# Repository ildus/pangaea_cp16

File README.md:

# Cabinet simulator (on impulse responses) based on AMT Pangaea CP-16

Contains schematic and pcb. Based on debugging board of CP16.

## Basic components.

* Pangaea CP-16
* NE5532D (3pcs) operational amplifiers.
* 0 Ohm 2512 SMD resistors
* 1206 SMD resistors
* 0805 SMD capacitors
* Electrolytic capacitors
* 15pin (pangaea), 4pin (pangaea control), 6pin (double potenciometer), and 2pcs of 2pin headers.
* 3pcs of 6.3mm audio jacks.
* 1pic of USB connector.

For the values of resistors and capacitors check the schematic.

## Pangaea CP-16 (copied from AMT website).

AMT Pangaea CP-16 module lets you to emulate any Guitar Cabinet sounding by loading appropriate
Guitar Cabinets’ Impulse Responses (IRs).

You can load up to 16 different Guitar Cabinets’ IRs in the module’s memory and choose the desired
one in the right moment. You can load IRs in the CP-16 memory and control their parameters via USB.

## Important note

As you can see on the image above, the pin header soldered on the side opposite to side with capacitor, that's not optimal and takes twice as much height. The PCB is designed to use with CP16 where pin header is soldered on the side of capacitor so the whole pcb can be put to usual aluminum case.

## PCB

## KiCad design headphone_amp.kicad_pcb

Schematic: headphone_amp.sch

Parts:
C1, C6, C13, C22, C24, C29, C30: 100n; C_0805_2012Metric
C2, C3, C4, C5: 47u; CP_Radial_D4.0mm_P2.00mm
C9, C10: 4.7u; C_0805_2012Metric
C12, C25, C26: 22p; C_0805_2012Metric
C14, C15: 470p; C_0805_2012Metric
C16, C17, C19: 1.2n; C_0805_2012Metric
C18: 0.22u; C_0805_2012Metric
C20, C21: 100p; C_0805_2012Metric
C27, C28: 220u; CP_Radial_D6.3mm_P2.50mm
D1: red; PinSocket_1x02_P2.00mm_Vertical
D2: BAV99; SOT-23
J1: btn; PinSocket_1x02_P2.54mm_Vertical
J2: AUX_IN; Jack6P
J3: IN; Jack6P
J4: pangea_cp16; PinSocket_1x15_P2.54mm_Vertical
J5: USB_A
J6: OUT; Jack6P
J7: PWR; PinSocket_1x02_P2.54mm_Vertical
J10: Conn_01x04; PinSocket_1x04_P2.54mm_Vertical
R1, R23: 68K; R_1206_3216Metric
R2, R30, R31, R36, R38, R39, R40: 0; R_2512_6332Metric
R5, R8, R9, R10, R11, R12, R26, R27, R34, R35: 100k; R_1206_3216Metric
R7: 2m; R_1206_3216Metric
R13: 150k; R_1206_3216Metric
R14, R15, R16, R17, R19, R20, R21, R22: 10k; R_1206_3216Metric
R18: 100; R_1206_3216Metric
R24, R25: 390k; R_1206_3216Metric
R28, R29: 10; R_1206_3216Metric
R32, R33: 2k; R_1206_3216Metric
R37: 3k; R_1206_3216Metric
RV2: B50K; PinSocket_1x06_P2.54mm_Vertical
U1, U3, U4: NE5532; SO-8_5.3x6.2mm_P1.27mm

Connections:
+4V: R9.2, R11.1, R12.1, R21.1, R22.1, R39.1, R39.2, U1.1, U1.2 (-)
+9V: C1.1, C2.1, C13.1, C22.2, C24.1, D1.2, D2.2, J4.15, J7.2, R2.1, R2.2, R5.2, R30.1, R30.2, R31.1, R31.2, R36.1, R36.2, U1.8 (V+), U3.8 (V+), U4.8 (V+)
/ain: J4.4, R38.1
/aoutl: C9.2, J4.2
/aoutr: C10.2, J4.1
/aux_l: C25.2, R24.2, R26.1, R35.1, U4.2 (-)
/aux_r: C26.2, R25.2, R27.1, R34.1, U4.6 (-)
/outl: J6.1, R28.1
/outr: J6.2, R29.1
/ps1: J4.13, J10.1
/ps2: J4.12, J10.2
/ps3: J4.11, J10.3
/ps4: J4.10, J10.4
Earth: J1.2, J7.1
GND: C1.2, C2.2, C3.2, C4.2, C5.2, C13.2, C14.2, C15.2, C19.2, C20.2, C21.2, C22.1, C24.2, D2.1, J1.1, J2.3, J2.4, J2.5, J3.3, J3.4, J4.3, J4.5, J4.14, J5.4, J5.5, J6.3, R7.2, R8.2, R32.1, R33.1, R37.2, U1.4 (V-), U3.4 (V-), U4.4 (V-)
unnamed: C3.1, RV2.6
unnamed: C4.1, R5.1, R8.1, U1.3 (+)
unnamed: C5.1, RV2.3
unnamed: C6.1, R10.2
unnamed: C6.2, J3.1, R7.1
unnamed: C9.1, R11.2, R14.1
unnamed: C10.1, R12.2, R15.1
unnamed: C12.1, C18.1, R13.1, U1.7
unnamed: C12.2, D2.3, R10.1, R13.2, U1.6 (-)
unnamed: C14.1, R14.2, R16.1
unnamed: C15.1, R15.2, R17.1
unnamed: C16.1, R1.1, U3.1, U3.2 (-)
unnamed: C16.2, R16.2, R19.1
unnamed: C17.1, R40.1, U3.6 (-), U3.7
unnamed: C17.2, R17.2, R20.1
unnamed: C18.2, R18.1
unnamed: C19.1, R18.2, R38.2
unnamed: C20.1, R19.2, U3.3 (+)
unnamed: C21.1, R20.2, U3.5 (+)
unnamed: C25.1, C27.1, R24.1, U4.1
unnamed: C26.1, C28.1, R25.1, U4.7
unnamed: C27.2, R28.2
unnamed: C28.2, R29.2
unnamed: C29.1, R35.2
unnamed: C29.2, J2.1, R32.2
unnamed: C30.1, R34.2
unnamed: C30.2, J2.2, R33.2
unnamed: D1.1, R37.1
unnamed: J4.6, J5.3
unnamed: J4.7, J5.2
unnamed: J4.8, J5.1
unnamed: R1.2, RV2.1
unnamed: R9.1, U1.5 (+)
unnamed: R21.2, U4.3 (+)
unnamed: R22.2, U4.5 (+)
unnamed: R23.1, R40.2
unnamed: R23.2, RV2.4
unnamed: R26.2, RV2.2
unnamed: R27.2, RV2.5

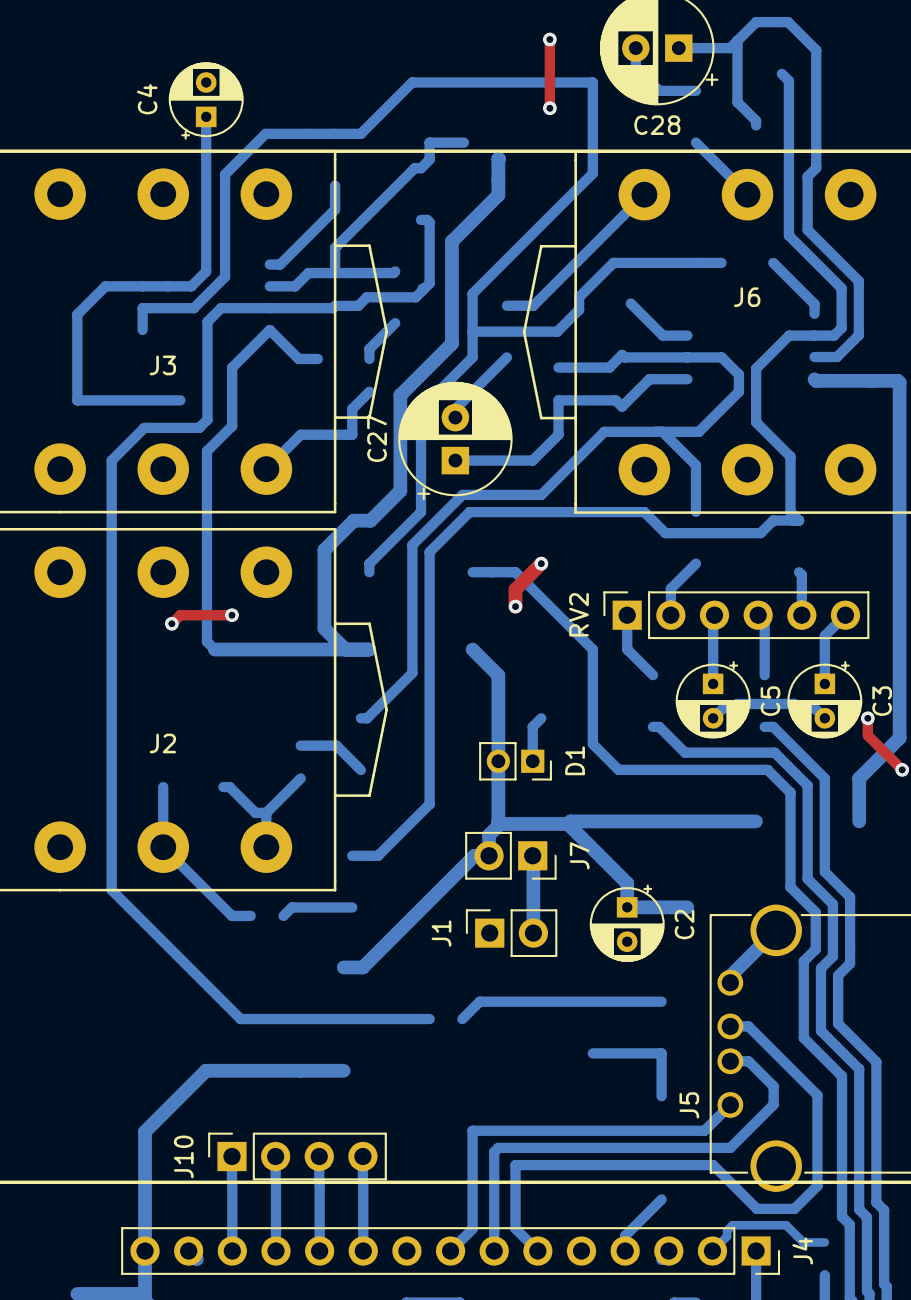
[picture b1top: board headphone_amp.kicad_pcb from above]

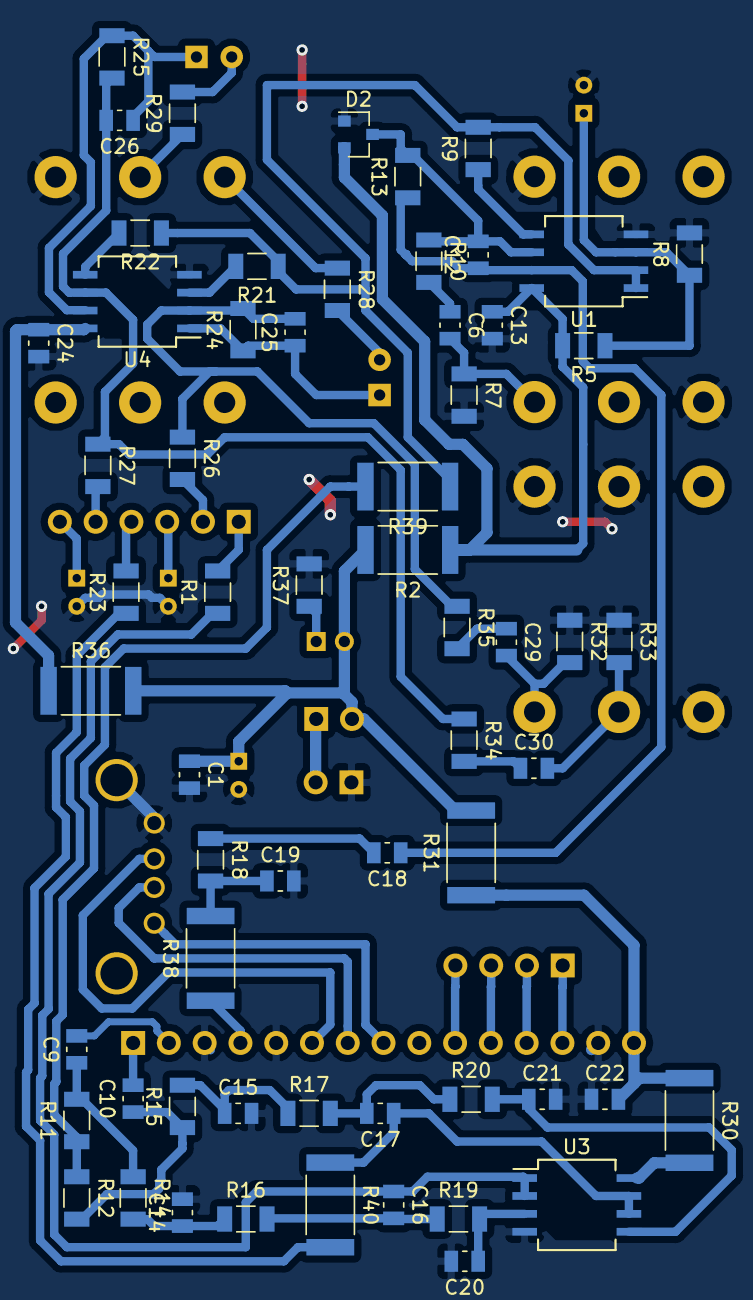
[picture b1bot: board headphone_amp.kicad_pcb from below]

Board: 2 copper layers, 77 parts (61 on the bottom side), 54 nets.

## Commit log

2018-05-08 initial
2018-05-30 working version
